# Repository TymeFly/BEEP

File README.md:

# BEEP
Ben Eater EEPROM Programmer (BEEP)

## Documentation

This repo contains code for a simple EEPROM programmer based on Ben Eater's EEPROM Programmer Design 
(https://github.com/beneater/eeprom-programmer)

While Ben's original design is a wonderful way to learn how to build a simple EEPROM programmer, there is 
a limitation in what it can do; the Arduino Nano application has to be clever enough to work out what to program the 
EEPROM with. This left me with two problems

1.	Every time I wanted to write a different EEPROM I’d have to write and download a new Arduino application.
2.	The Arduino has a limited about of memory – less than that of the EEPROMs it’s trying to write. 
    To program a more complex EEPROM it becomes difficult to write an application that is small enough to 
	fit into the Arduino

My solution is to split the job in half; the embedded Arduino application knows how to perform basic EEPROM
related tasks but knows nothing about any specific EEPROM, and a Java client that can manage the programmer. 
This client can download specific EEPROM data to the programmer in (very) small chunks, and thus get around the
memory and complexity limits.

### The embedded Arduino application.

The embedded application communicates with the Java client through the serial port at 57600 baud.
It understands the following commands:

* d[start[:end]]

  Dump EEPROM contents.'start' defaults to 0. 'end' defaults to 0x1fff

* f[:start[:end[:hex]]]  

  Fill EEPROM between 'start' and 'end' with 'hex'.'start' defaults to 0, 'end' defaults to 0x1fff, 'val' defaults to 0

* e

  Fill the EEPROM with 0xff

* t

  Fill EEPROM with a test sequence and read it back

* pstart,len            

  Enter Programming mode. 'start' address of first byte to write,'number' of bytes to write
  
* \-                    

  Redisplay the command prompt
						
* \?

  Display the commands available

All values are given in Hex

### The Java based CLI 

To use the CLI be sure to download and compile my S-Rec library first (https://github.com/TymeFly/S-Rec)

#### Usage:
  java com.github.tymefly.beep.Main  --programmerTimeout N --readTimeout N --writeTimeout N -p (--port) N

 [dump | fill | ping | erase | test | program | verify | upload | describe]

-p (--port) N            COM port programmer is connected to

--programmerTimeout N    timeout in milliseconds when waiting  for programmer to respond (default:  10000)

--readTimeout N          read timeout in milliseconds when waiting reading the COM port  (default: 1000)

--writeTimeout N         write timeout in milliseconds when waiting reading the COM port (default: 100)

#### File Formats:

When uploading data from an EEPROM the generated file will always be in SRecord format - see https://en.wikipedia.org/wiki/SREC_(file_format)
When downloading data into an EEPROM the application can use the following file formats:
-	SRecord (.s19, .s28, .s37, .s, .s1, .s2, .s3, .sx, .srec, .mot, .mx)
-	Binary files (.raw, .dat, .data, .bin)

#### Examples:

 java com.github.tymefly.beep.Main  -?   
-	Display the help page

 java com.github.tymefly.beep.Main  -p 7 ping
-	Ping the Arduino application to see if it can communicate

 java com.github.tymefly.beep.Main  -p 7 dump --start 0x20 --end 0x46
-	Display the content of the EEPROM on the screen (Standard Out) in hex and ASCII 

 java com.github.tymefly.beep.Main  -p 7 erase
-	Erase the EEPROM (write 0xff to all locations)

 java com.github.tymefly.beep.Main  -p 7 fill --byte 0x5a --start 0x100 --end 0x200
-	Write the value 0x5a to all locations in the EEPROM between 0x100 and 0x200

 java com.github.tymefly.beep.Main  -p 7 test
-	Write a test pattern to all locations in the EEPROM and check they have been written correctly

 java com.github.tymefly.beep.Main  -p 7 program --file MyFile.srec
-	Write the content of MyFile.srec to the EERPOM

 java com.github.tymefly.beep.Main  -p 7 upload --header "My Description" --out MyFile.srec
-	Read the content of the EEPROM and write it to MyFile.srec to 

 java com.github.tymefly.beep.Main  -p 7 verify --MyFile.srec --maxErrors 2
-	Check that the EEPROM contains the content of MyFile. Give up after 2 errors.

 java com.github.tymefly.beep.Main  describe --file MyFile.srec
-	Dump the SRecord metadata to standard out. This includes the start address, end address, images size
    and all header fields
	
## Libraries used

* My own S-Rec library for reading/writing S-Records files (https://github.com/TymeFly/S-Rec)
* JSR305 for documenting null object references
* args4j for handling the CLI parsing

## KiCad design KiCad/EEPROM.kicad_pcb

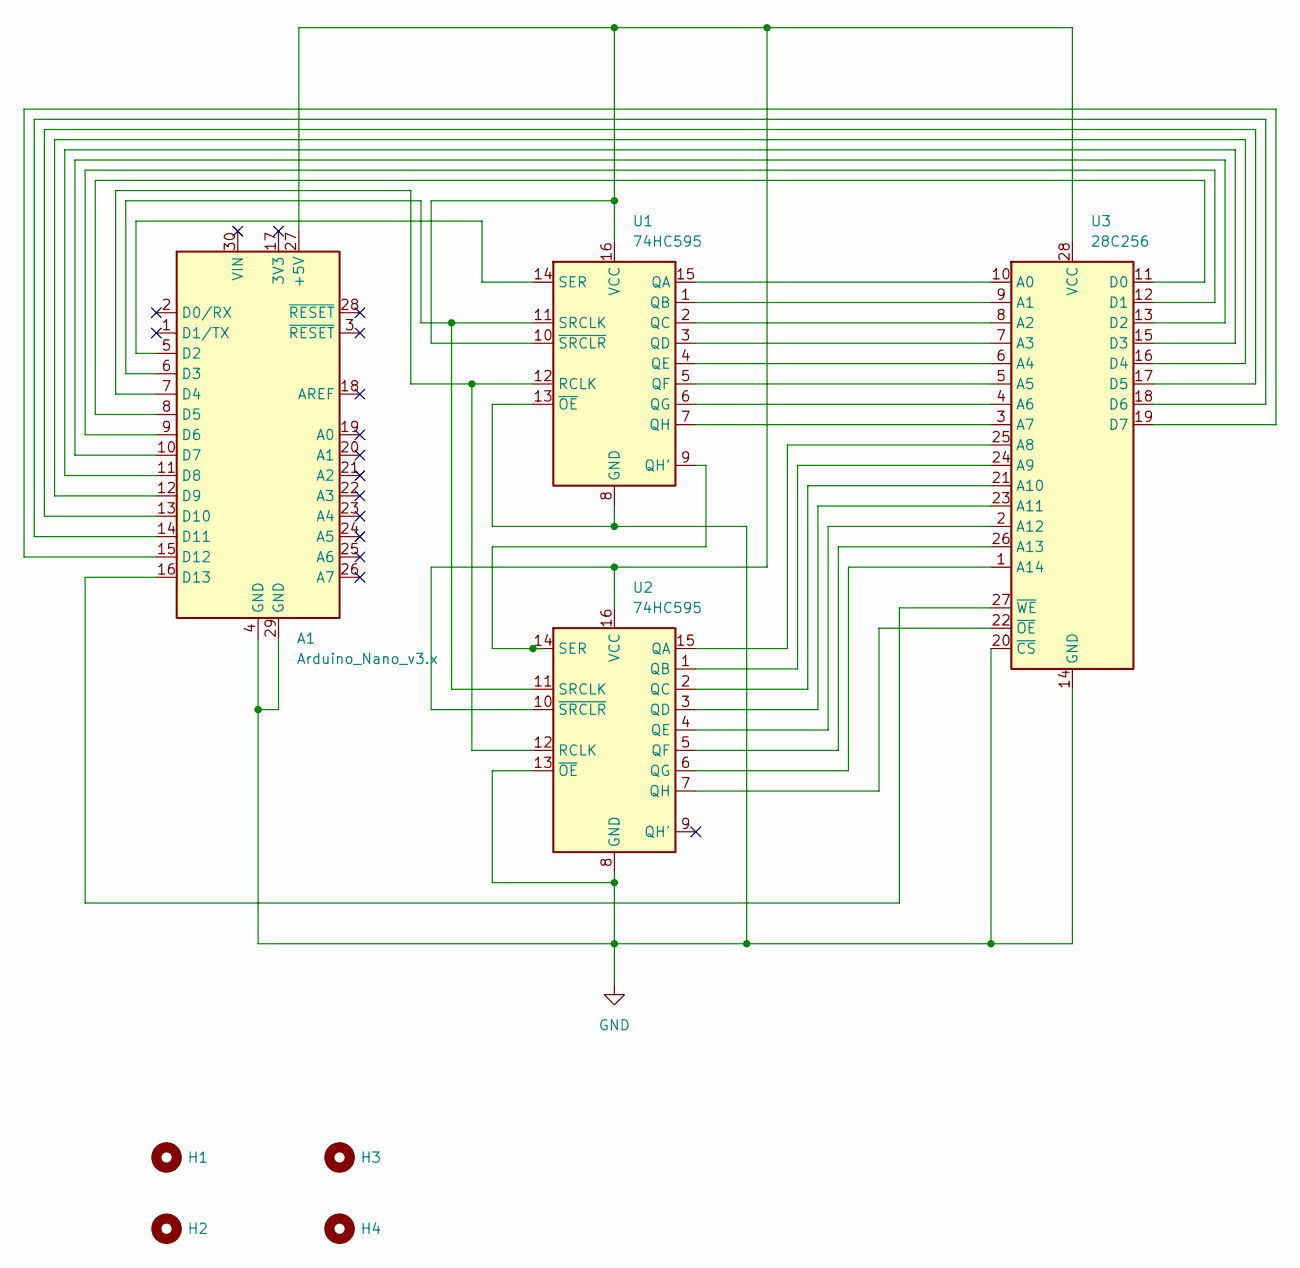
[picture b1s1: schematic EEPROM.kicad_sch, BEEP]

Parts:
A1: Arduino_Nano_v3.x; Arduino_Nano
H1, H2, H3, H4: MountingHole_2.7mm_M2.5
U1, U2: 74HC595; DIP-16_W7.62mm_Socket_LongPads
U3: 28C256; DIP-28_W15.24mm_Socket_LongPads

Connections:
GND: A1.4 (GND), A1.29 (GND), U1.8 (GND), U1.13 (~OE), U2.8 (GND), U2.13 (~OE), U3.14 (GND), U3.20 (~CS)
unnamed: A1.27 (+5V), U1.10 (~SRCLR), U1.16 (VCC), U2.10 (~SRCLR), U2.16 (VCC), U3.28 (VCC)
unnamed: A1.5 (D2), U1.14 (SER)
unnamed: A1.6 (D3), U1.11 (SRCLK), U2.11 (SRCLK)
unnamed: A1.7 (D4), U1.12 (RCLK), U2.12 (RCLK)
unnamed: A1.8 (D5), U3.11 (D0)
unnamed: A1.9 (D6), U3.12 (D1)
unnamed: A1.10 (D7), U3.13 (D2)
unnamed: A1.11 (D8), U3.15 (D3)
unnamed: A1.12 (D9), U3.16 (D4)
unnamed: A1.13 (D10), U3.17 (D5)
unnamed: A1.14 (D11), U3.18 (D6)
unnamed: A1.15 (D12), U3.19 (D7)
unnamed: A1.16 (D13), U3.27 (~WE)
unnamed: U1.15 (QA), U3.10 (A0)
unnamed: U1.1 (QB), U3.9 (A1)
unnamed: U1.2 (QC), U3.8 (A2)
unnamed: U1.3 (QD), U3.7 (A3)
unnamed: U1.4 (QE), U3.6 (A4)
unnamed: U1.5 (QF), U3.5 (A5)
unnamed: U1.6 (QG), U3.4 (A6)
unnamed: U1.9 (QH'), U2.14 (SER)
unnamed: U1.7 (QH), U3.3 (A7)
unnamed: U2.15 (QA), U3.25 (A8)
unnamed: U2.1 (QB), U3.24 (A9)
unnamed: U2.2 (QC), U3.21 (A10)
unnamed: U2.3 (QD), U3.23 (A11)
unnamed: U2.4 (QE), U3.2 (A12)
unnamed: U2.5 (QF), U3.26 (A13)
unnamed: U2.6 (QG), U3.1 (A14)
unnamed: U2.7 (QH), U3.22 (~OE)

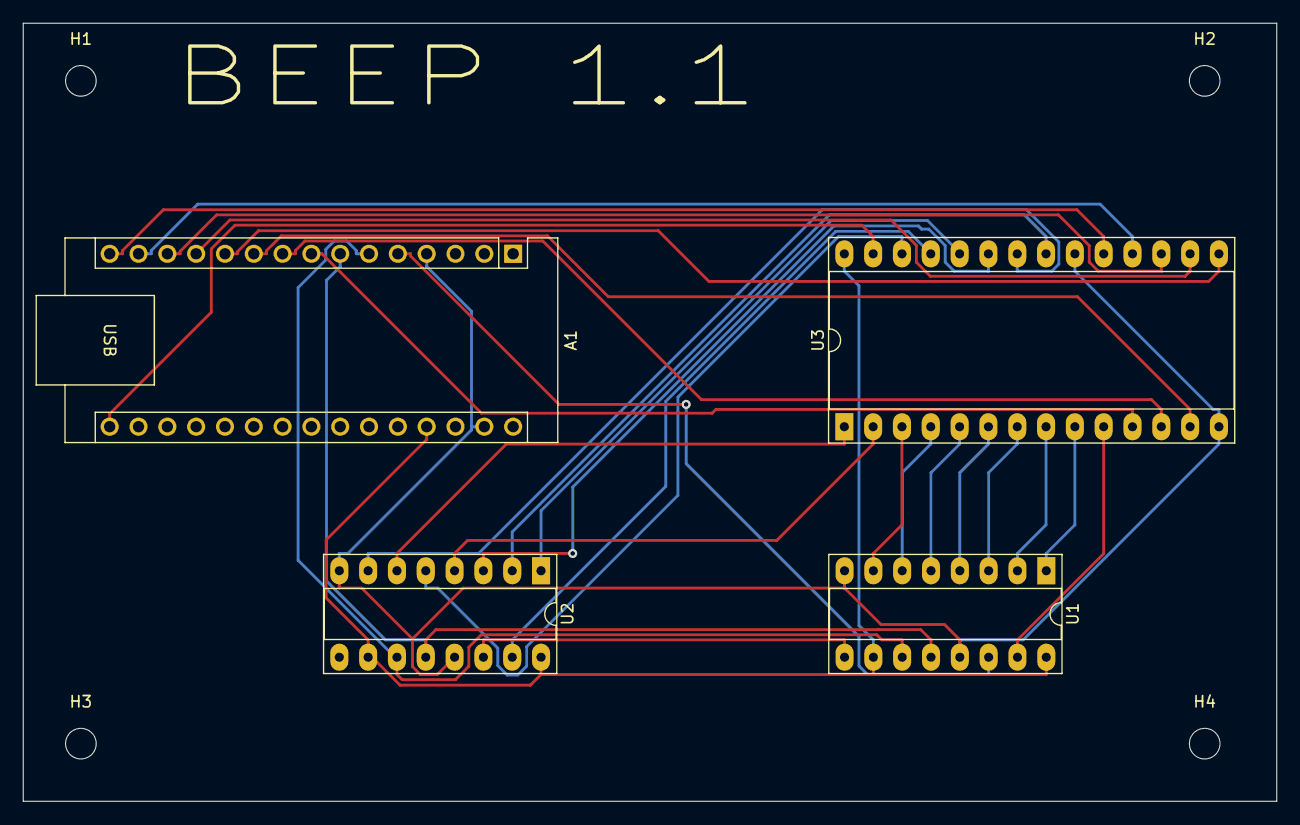
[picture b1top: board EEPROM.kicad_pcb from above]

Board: 2 copper layers, 110.5 x 68.6 mm, 8 parts (0 on the bottom side), 31 nets.

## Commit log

2019-08-10 Fix up Readme
2019-11-03 Support for downloading binary files
2020-03-17 repackage
2020-08-16 Move to Java 11. Bump tools
2020-08-16 Add command "describe" to dump the SRec metadata with out uploading
2020-08-16 Update documentation
2024-09-07 Add KiCad design. Programmer reports number of failures. CLI program has --dump option
